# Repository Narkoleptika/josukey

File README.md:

# Josukey

A keyboard for Joey

This is an ergogen based corne clone that I intend to modify and tweak as I descend into the rabbit hole

## V1

## Prerequisites

* Node
* Docker
## Getting Started

Get my files on your computer 😏 and install dependencies.

```bash
git clone https://github.com/Narkoleptika/josukey.git
cd josukey
npm i
```

## Ergogen

### Build

This will run Ergogen and build all of the output files.

```bash
npm run ergogen:build
```

### Watch

This will watch the `config.yaml` file and the `footprints` directory and run the build command whenever there are changes.

```bash
npm run ergogen:watch
```

## ZMK

### Init

Downloads ZMK dependencies

```bash
npm run zmk:update
```

### Build

Builds the ZMK firmware

```bash
npm run zmk:build
```

### Down

Shuts down the ZMK docker services

```bash
npm run zmk:down
```

## Thanks

* <a href="https://github.com/ergogen/ergogen" target="_blank">Ergogen</a>
* <a href="https://discord.gg/nbKcAZB" target="_blank">Absolem Club Discord</a>
* <a href="https://github.com/tsteffek/Ergogen-V4-Migration-Guide" target="_blank">V4 Migration Guide</a>
* <a href="https://gitlab.com/Audijo/keyboard" target="_blank">Claw</a>
* <a href="https://github.com/MrCarney/mrkeyboard" target="_blank">MrKeyboard</a>
* <a href="https://github.com/foostan/crkbd" target="_blank">Corne keyboard</a>
* <a href="https://github.com/zmkfirmware/zmk" target="_blank">ZMK</a>
* <a href="https://github.com/manna-harbour/miryoku_zmk" target="_blank">Miryoku ZMK</a>

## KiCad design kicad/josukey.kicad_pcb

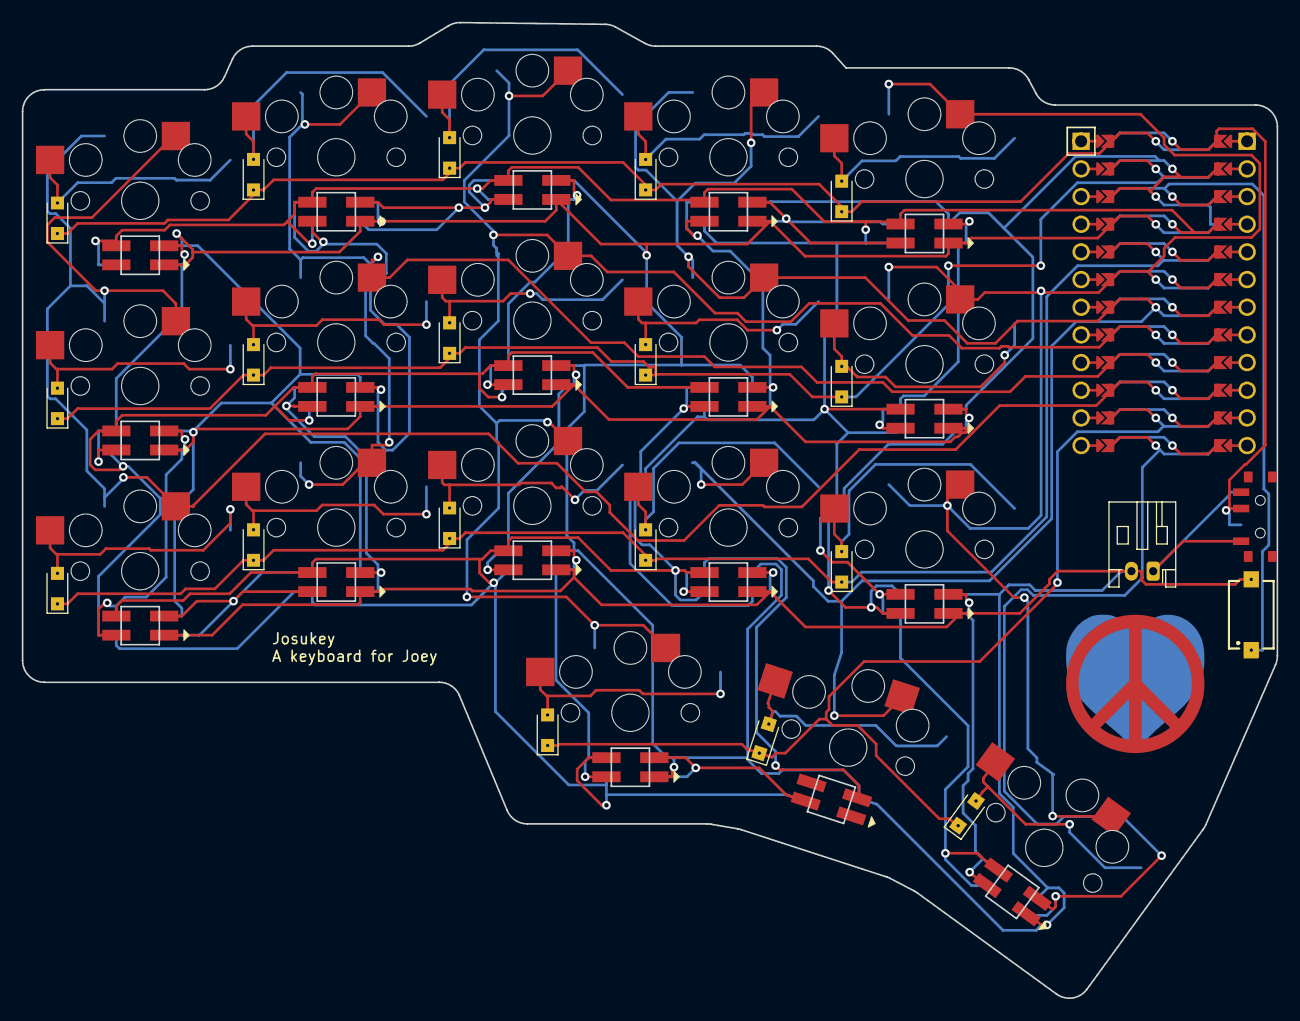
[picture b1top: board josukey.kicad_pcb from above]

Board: 2 copper layers, 115.2 x 89.6 mm, 58 parts (0 on the bottom side), 50 nets.

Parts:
D1, D2, D3, D4, D5, D6, D7, D8, D9, D10, D11, D12, D13, D14, D15, D16, D17, D18: Nexperia_CFP3_SOD-123W
LED1, LED2, LED3, LED4, LED5, LED6, LED7, LED8, LED9, LED10, LED11, LED12, LED13, LED14, LED15, LED16, LED17, LED18: WS2812B
MCU1: ProMicro
S1, S2, S3, S4, S5, S6, S7, S8, S9, S10, S11, S12, S13, S14, S15, S16, S17, S18: PG1350
S19: 434121025816
T1: SW_SPDT_PCM12
_1: JST_PH_S2B-PH-K_1x02_P2.00mm_Horizontal

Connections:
GND: LED1.3, LED2.3, LED3.3, LED4.3, LED5.3, LED6.3, LED7.3, LED8.3, LED9.3, LED10.3, LED11.3, LED12.3, LED13.3, LED14.3, LED15.3, LED16.3, LED17.3, LED18.3, MCU1.2, MCU1.21, MCU1.22, S19.2, _1.2
P0: D2.1, D5.1, D8.1, D11.1, D14.1, MCU1.23
P1: D3.1, D6.1, D9.1, D12.1, D15.1, MCU1.24
P2: D1.1, D4.1, D7.1, D10.1, D13.1, MCU1.20
P3: MCU1.19, S13.1, S14.1, S15.1, S18.1
P4: MCU1.18, S10.1, S11.1, S12.1, S17.1
P5: MCU1.17, S7.1, S8.1, S9.1, S16.1
P6: MCU1.16, S4.1, S5.1, S6.1
P7: MCU1.15, S1.1, S2.1, S3.1
P8: D16.1, D17.1, D18.1, MCU1.14
P9: LED18.4, MCU1.13
RAW: MCU1.1, T1.2
RST: MCU1.3, S19.1
VCC: LED1.1, LED2.1, LED3.1, LED4.1, LED5.1, LED6.1, LED7.1, LED8.1, LED9.1, LED10.1, LED11.1, LED12.1, LED13.1, LED14.1, LED15.1, LED16.1, LED17.1, LED18.1, MCU1.4
main_index_bottom: D10.2, S10.2
main_index_home: D11.2, S11.2
main_index_top: D12.2, S12.2
main_inner_bottom: D13.2, S13.2
main_inner_home: D14.2, S14.2
main_inner_top: D15.2, S15.2
main_middle_bottom: D7.2, S7.2
main_middle_home: D8.2, S8.2
main_middle_top: D9.2, S9.2
main_pinky_bottom: D1.2, S1.2
main_pinky_home: D2.2, S2.2
main_pinky_top: D3.2, S3.2
main_ring_bottom: D4.2, S4.2
main_ring_home: D5.2, S5.2
main_ring_top: D6.2, S6.2
pos: T1.1, _1.1
rgb_main_index_bottom: LED10.4, LED11.2
rgb_main_index_home: LED11.4, LED12.2
rgb_main_index_top: LED12.4, LED15.2
rgb_main_inner_bottom: LED13.4, LED18.2
rgb_main_inner_home: LED13.2, LED14.4
rgb_main_inner_top: LED14.2, LED15.4
rgb_main_middle_bottom: LED7.4, LED16.2
rgb_main_middle_home: LED7.2, LED8.4
rgb_main_middle_top: LED8.2, LED9.4
rgb_main_pinky_bottom: LED1.4, LED4.2
rgb_main_pinky_home: LED1.2, LED2.4
rgb_main_pinky_top: LED2.2, LED3.4
rgb_main_ring_bottom: LED4.4, LED5.2
rgb_main_ring_home: LED5.4, LED6.2
rgb_main_ring_top: LED6.4, LED9.2
rgb_thumb_home_home: LED10.2, LED17.4
rgb_thumb_inner_home: LED16.4, LED17.2
thumb_home_home: D17.2, S17.2
thumb_inner_home: D16.2, S16.2
thumb_outer_home: D18.2, S18.2

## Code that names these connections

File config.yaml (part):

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                    rows:
                        bottom:
                            led_in: "rgb_{{name}}"
                            led_out: rgb_main_pinky_home
                        home:
                            led_in: "rgb_{{name}}"
                            led_out: rgb_main_pinky_top
                        top:
                            led_in: "rgb_{{name}}"
                ring:
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                    rows:
                        bottom:
                            led_in: "rgb_{{name}}"
                            led_out: rgb_main_pinky_bottom
                        home:
                            led_in: "rgb_{{name}}"
                            led_out: rgb_main_ring_bottom
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                -   ref: thumb_inner_home
                    shift: [-0.6cx, -0.6cy]

                -   ref: main_pinky_bottom
                    shift: [1.6cx, -0.6cy]
                -   ref: main_pinky_bottom
                    shift: [0.6cx, -0.6cy]
                -   ref: main_pinky_bottom
                    shift: [-0.6cx, -0.6cy]

                -   ref: main_pinky_top
                    shift: [-0.6cx, 0.6cy]
                -   ref: main_pinky_top
                    shift: [0.4cx, 0.6cy]

                -   ref: main_ring_top
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            #     # GND
            #     P2:  main_middle_top
            #     P3:  main_ring_top
            #     P4:  main_pinky_top
            #     P5:  main_inner_home
            #     P6:  main_index_home
            #     P7:  main_middle_home
            #     P8:  main_ring_home
            #     P9:  main_pinky_home
            #     # right
            #     # RAW
            #     # GND
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            #     P21: thumb_outer_home
            #     P20: thumb_home_home
            #     P19: thumb_inner_home
            #     P18: main_pinky_bottom
            #     P15: main_ring_bottom
            #     P14: main_middle_bottom
            #     P16: main_index_bottom
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        front_text: &text
            what: text
            where: &textWhere
                ref: main_pinky_bottom
                shift: [12, -7]
            params: &textParams
                text: Josukey\nA keyboard for Joey
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
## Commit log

2023-03-10 add image
2023-03-10 gratitude
2023-03-11 checkpoint
2023-03-12 update pinout and layout
2023-03-12 make silk layer reveseable
2023-03-12 add images
2023-03-12 add initial round of kicad files
2023-03-13 add text and include images in ergogen config
2023-03-23 Get to a point where autoroute works decently well
2023-03-23 Remove manual vias and routing
2023-03-23 Update image
2023-03-23 Restore former logo size. Update kicad with autorouted pcb
2023-03-23 version bump
2023-03-23 remove more dead code
2023-03-27 Move ergogen to subdir
2023-03-27 add initial zmk setup with miryoku
2023-03-27 change led pin to high frequency and add case and screw holes
2023-03-27 outline fixes
2023-03-27 fix ergogen:watch
2023-03-28 add controller overlay and screw holes
2023-03-28 more thanks
2023-04-12 shape improvements
2023-04-16 Fix off by one error and folder name
2023-04-16 Add settings reset to build
2023-04-16 we have liftoff
2023-04-16 update README with finished v1 build
2023-04-30 switch to updated pinctrl thing
2023-05-01 add flag
